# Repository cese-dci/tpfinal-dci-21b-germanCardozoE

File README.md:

## Trabajo práctico final de la asignatura DCI ##
Este repositorio contiene el trabajo práctico final para la asignatura de Diseño de Circuitos Impresos de la carrera de posgrado de FIUBA.

* Autor: Cardozo Germán Eloy
* Título corto del trabajo:  ESP32-CAM
* Descripción:  El siguiente proyecto incluye tanto el circuito esquemático como el diseño del PCB realizado en kicad. A su vez se anexan diversas hojas de datos y bibliotecas utilizadas en su desarrollo.
ESP32-CAM es un módulo WiFi y Bluetooth que integra una pequeña cámara por lo que puede funcionar de manera independiente.
La camara OV2640 de 2MP integra un sensor de imagen CMOS UXGA (1632*1232) de 1/4 de pulgada. El pequeño tamaño del sensor y el bajo voltaje de operación brindan todas las características de una sola cámara UXGA y un procesador de imágenes. A través del control de bus SCCB, puede generar datos de imagen de 8/10 bits de varias resoluciones, como fotograma completo, submuestreo, zoom y ventanas.
La imagen UXGA de esta camara puede alcanzar hasta 15 cuadros por segundo (hasta 30 cuadros para SVGA y 60 cuadros para CIF). Los usuarios tienen un control completo sobre la calidad de la imagen, el formato de datos y la transmisión.
Todas las funciones de procesamiento de imágenes, incluida la curva gamma, el balance de blancos, el contraste, el croma, etc. se pueden programar a través de la interfaz SCCB.
Los sensores de imagen Omni Vision utilizan una tecnología de sensor única para mejorar la calidad de la imagen y reducir las imágenes en color nítidas y estables mediante la reducción o eliminación de defectos ópticos o electrónicos, como el ruido de patrón fijo, manchas y flotación.

## Principales Características ##
• Modelo: ESP32-CAM + Cámara OV2640
• Voltaje de Alimentación ESP 32 CAM: 5V
• Módulo Wi-Fi BT 802.11b/g/n
• Tipo de cámara: OV2640 2MP
• El modulo ESP 32CAM tiene CPU 32 bits de doble núcleo de baja potencia
• Frecuencia principal de hasta 240 MHz
• Potencia informática de hasta 600 DMIPS
• Velocidad de reloj de hasta 160 MHz
• Incorpora SRAM 520Kb, 4MPSRAM externa
• El modulo ESP-32 CAM Soporta interfaces: UART / SPI / I2C / PWM / ADC / DAC
• El modulo ESP-32-CAM Soporta cámaras OV2640 y OV7670, Flash Incorporado
• El modulo ESP 32-CAM Soporta tarjetas TF micro SD (Máximo 4 GB)
• El modulo ESP-32CAM Soporta la carga de imagen WiFi
• Compatible con modos de operación STA / AP / STA+AP
• Con antena PCB
• El modulo ESP32CAM integra conectores u.FL y FPC

## Licencia de este trabajo ##
Licencia GNU GPL

## Estructura del TP FINAL ##

Se propone y se pide utilizar la siguiente estructura.

* doc: Toda la información sobre el circuito, principalmente de autoría o procesamiento propio. Por ejemplo:
  * Notas de ingeniería propias.
  * Notas de aplicación propias.
  * Estudios previos, estado del arte, resumen de las investigaciones.
  * Notas con cálculos.
  * Dibujos adicionales.
  * Fotos de los prototipos.
  * Presupuestos, cotizaciones.
* info: Toda la iformación recolectada, principalmente de terceros, como por ejemplo:
  * Hojas de datos.
  * Notas de aplicación.
  * Info de productos comerciales.
  * Info en internet.
* pcb: Archivos de diseño esquemático y pcb.

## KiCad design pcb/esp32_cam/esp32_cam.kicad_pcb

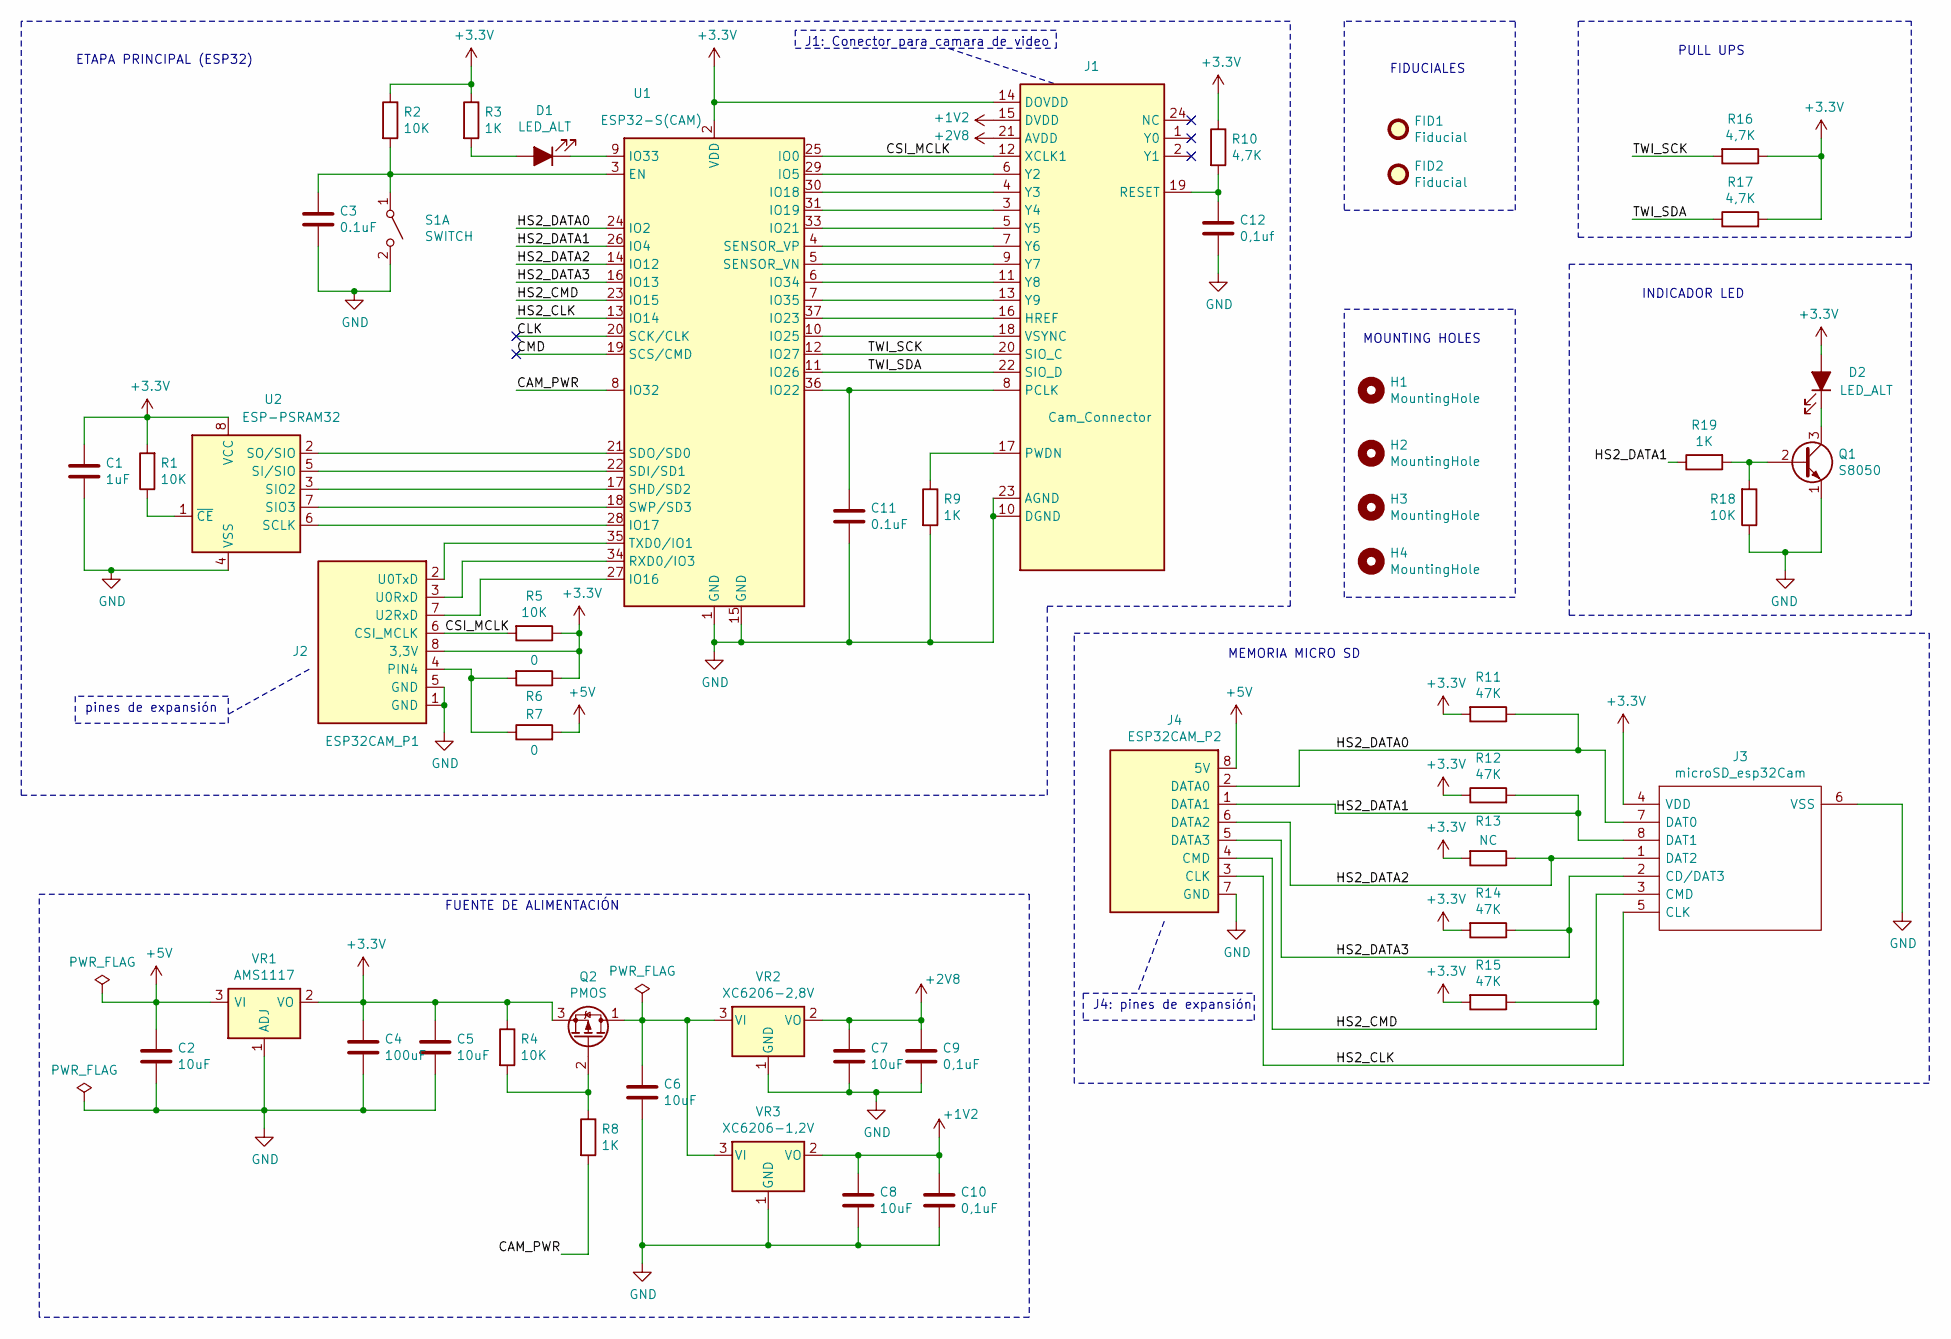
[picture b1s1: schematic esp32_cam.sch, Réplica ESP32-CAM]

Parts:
C1: 1uF; C_0805_2012Metric
C2, C5, C6, C7, C8: 10uF; C_0805_2012Metric
C3, C11: 0.1uF; C_0805_2012Metric
C4: 100uF; C_0805_2012Metric
C9, C10: 0,1uF; C_0805_2012Metric
C12: 0,1uf; C_0805_2012Metric
D1: LED_ALT; LED_1206_3216Metric_Pad1.42x1.75mm_HandSolder
D2: LED_ALT; LED_2816_7142Metric_Castellated
FID1, FID2: Fiducial; Fiducial_0.5mm_Mask1mm
H1, H2: MountingHole; MountingHole_2.5mm
H3, H4: MountingHole; MountingHole_2.1mm
J1: Cam_Connector; TE_2-1734839-4_1x24-1MP_P0.5mm_Horizontal
J2: ESP32CAM_P1; PinHeader_1x08_P2.54mm_Vertical
J3: microSD_esp32Cam; DM3ATSFPEJM5; Manufacturer_Part_Number DM3AT-SF-PEJM5; Mouser Part Number 798-DM3AT-SF-PEJM5
J4: ESP32CAM_P2; PinHeader_1x08_P2.54mm_Vertical
Q1: S8050; SOT-23
Q2: PMOS; SOT-23
R1, R2, R4, R5, R18: 10K; R_0805_2012Metric
R3, R8, R9, R19: 1K; R_0805_2012Metric
R6, R7: 0; R_0805_2012Metric
R10, R16, R17: 4,7K; R_0805_2012Metric
R11, R12, R14, R15: 47K; R_0805_2012Metric
R13: NC; R_0805_2012Metric
S1: SWITCH; SW_SPST_B3U-1000P
U1: ESP32-S(CAM); ESP32-WROOM-32U
U2: ESP-PSRAM32; SOIC-8_3.9x4.9mm_P1.27mm
VR1: AMS1117; SOT-223-3_TabPin2
VR2: XC6206-2,8V; SOT-23
VR3: XC6206-1,2V; SOT-23

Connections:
+1V2: C8.2, C10.2, J1.15 (DVDD), VR3.2 (VO)
+2V8: C7.2, C9.2, J1.21 (AVDD), VR2.2 (VO)
+3V3: C1.2, C4.2, C5.2, D2.2 (A), J1.14 (DOVDD), J2.8 (3,3V), J3.4 (VDD), Q2.3 (S), R1.2, R2.1, R3.1, R4.1, R5.1, R6.1, R10.1, R11.2, R12.1, R13.2, R14.2, R15.2, R16.1, R17.2, U1.2 (VDD), U2.8 (VCC), VR1.2 (VO)
+5V: C2.2, J4.8 (5V), R7.2, VR1.3 (VI)
/CAM_PWR: R8.2, U1.8 (IO32)
/CLK: U1.20 (SCK/CLK)
/CMD: U1.19 (SCS/CMD)
/CSI_MCLK: J1.12 (XCLK1), J2.6 (CSI_MCLK), R5.2, U1.25 (IO0)
/HS2_CLK: J3.5 (CLK), J4.3 (CLK), U1.13 (IO14)
/HS2_CMD: J3.3 (CMD), J4.4 (CMD), R15.1, U1.23 (IO15)
/HS2_DATA0: J3.7 (DAT0), J4.2 (DATA0), R11.1, U1.24 (IO2)
/HS2_DATA1: J3.8 (DAT1), J4.1 (DATA1), R12.2, R19.1, U1.26 (IO4)
/HS2_DATA2: J3.1 (DAT2), J4.6 (DATA2), R13.1, U1.14 (IO12)
/HS2_DATA3: J3.2 (CD/DAT3), J4.5 (DATA3), R14.1, U1.16 (IO13)
/TWI_SCK: J1.20 (SIO_C), R16.2, U1.12 (IO27)
/TWI_SDA: J1.22 (SIO_D), R17.1, U1.11 (IO26)
GND: C1.1, C2.1, C3.1, C4.1, C5.1, C6.1, C7.1, C8.1, C9.1, C10.1, C11.2, C12.2, J1.10 (DGND), J1.23 (AGND), J2.1 (GND), J2.5 (GND), J3.6 (VSS), J4.7 (GND), Q1.1 (E), R9.2, R18.1, S1.2 (B), U1.1 (GND), U1.15 (GND), U1.38 (GND), U1.39 (GND), U2.4 (VSS), VR1.1 (ADJ), VR2.1 (GND), VR3.1 (GND)
unnamed: C3.2, R2.2, S1.1 (A), U1.3 (EN)
unnamed: C6.2, Q2.1 (D), VR2.3 (VI), VR3.3 (VI)
unnamed: C11.1, J1.8 (PCLK), U1.36 (IO22)
unnamed: C12.1, J1.19 (RESET), R10.2
unnamed: D1.1 (K), U1.9 (IO33)
unnamed: D1.2 (A), R3.2
unnamed: D2.1 (K), Q1.3 (C)
unnamed: J1.3 (Y4), U1.31 (IO19)
unnamed: J1.4 (Y3), U1.30 (IO18)
unnamed: J1.5 (Y5), U1.33 (IO21)
unnamed: J1.6 (Y2), U1.29 (IO5)
unnamed: J1.7 (Y6), U1.4 (SENSOR_VP)
unnamed: J1.9 (Y7), U1.5 (SENSOR_VN)
unnamed: J1.11 (Y8), U1.6 (IO34)
unnamed: J1.13 (Y9), U1.7 (IO35)
unnamed: J1.16 (HREF), U1.37 (IO23)
unnamed: J1.17 (PWDN), R9.1
unnamed: J1.18 (VSYNC), U1.10 (IO25)
unnamed: J2.2 (U0TxD), U1.35 (TXD0/IO1)
unnamed: J2.3 (U0RxD), U1.34 (RXD0/IO3)
unnamed: J2.4 (PIN4), R6.2, R7.1
unnamed: J2.7 (U2RxD), U1.27 (IO16)
unnamed: Q1.2 (B), R18.2, R19.2
unnamed: Q2.2 (G), R4.2, R8.1
unnamed: R1.1, U2.1 (~CE)
unnamed: U1.17 (SHD/SD2), U2.3 (SIO2)
unnamed: U1.18 (SWP/SD3), U2.7 (SIO3)
unnamed: U1.21 (SDO/SD0), U2.2 (SO/SIO)
unnamed: U1.22 (SDI/SD1), U2.5 (SI/SIO)
unnamed: U1.28 (IO17), U2.6 (SCLK)

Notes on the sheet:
PULL UPS
INDICADOR LED
FUENTE DE ALIMENTACIÓN
MEMORIA MICRO SD
MOUNTING HOLES
ETAPA PRINCIPAL (ESP32)
FIDUCIALES
J1: Conector para camara de video
J4: pines de expansión
pines de expansión

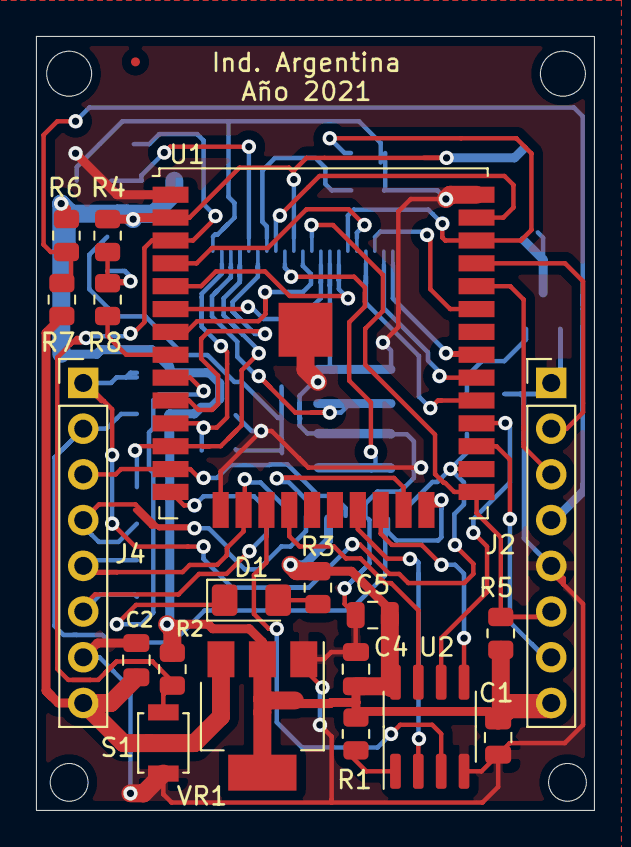
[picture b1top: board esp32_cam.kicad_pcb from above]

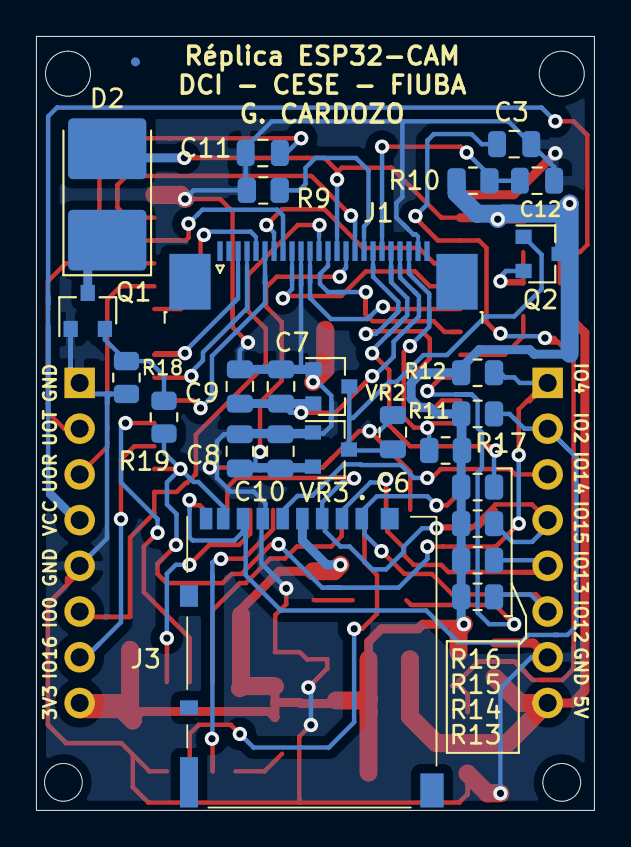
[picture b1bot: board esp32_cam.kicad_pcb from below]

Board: 2 copper layers, 31.0 x 43.0 mm, 51 parts (27 on the bottom side), 45 nets.

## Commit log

2021-08-09 carga de esquematico completo
2021-08-13 correcciones de esquematico y se agrega y completa información
2021-08-14 se sube primera versión del PCB
2021-08-16 se sube versión final y se agrega documentación
2021-08-16 se corrige el README principal
2021-08-16 se agrega introducción del modulo ESP32-CAM
2021-08-16 se corrige serigrafía
2021-08-17 se crea la carpeta shapes3D
2021-08-20 se amplia el clearence de 0.2 0.25
